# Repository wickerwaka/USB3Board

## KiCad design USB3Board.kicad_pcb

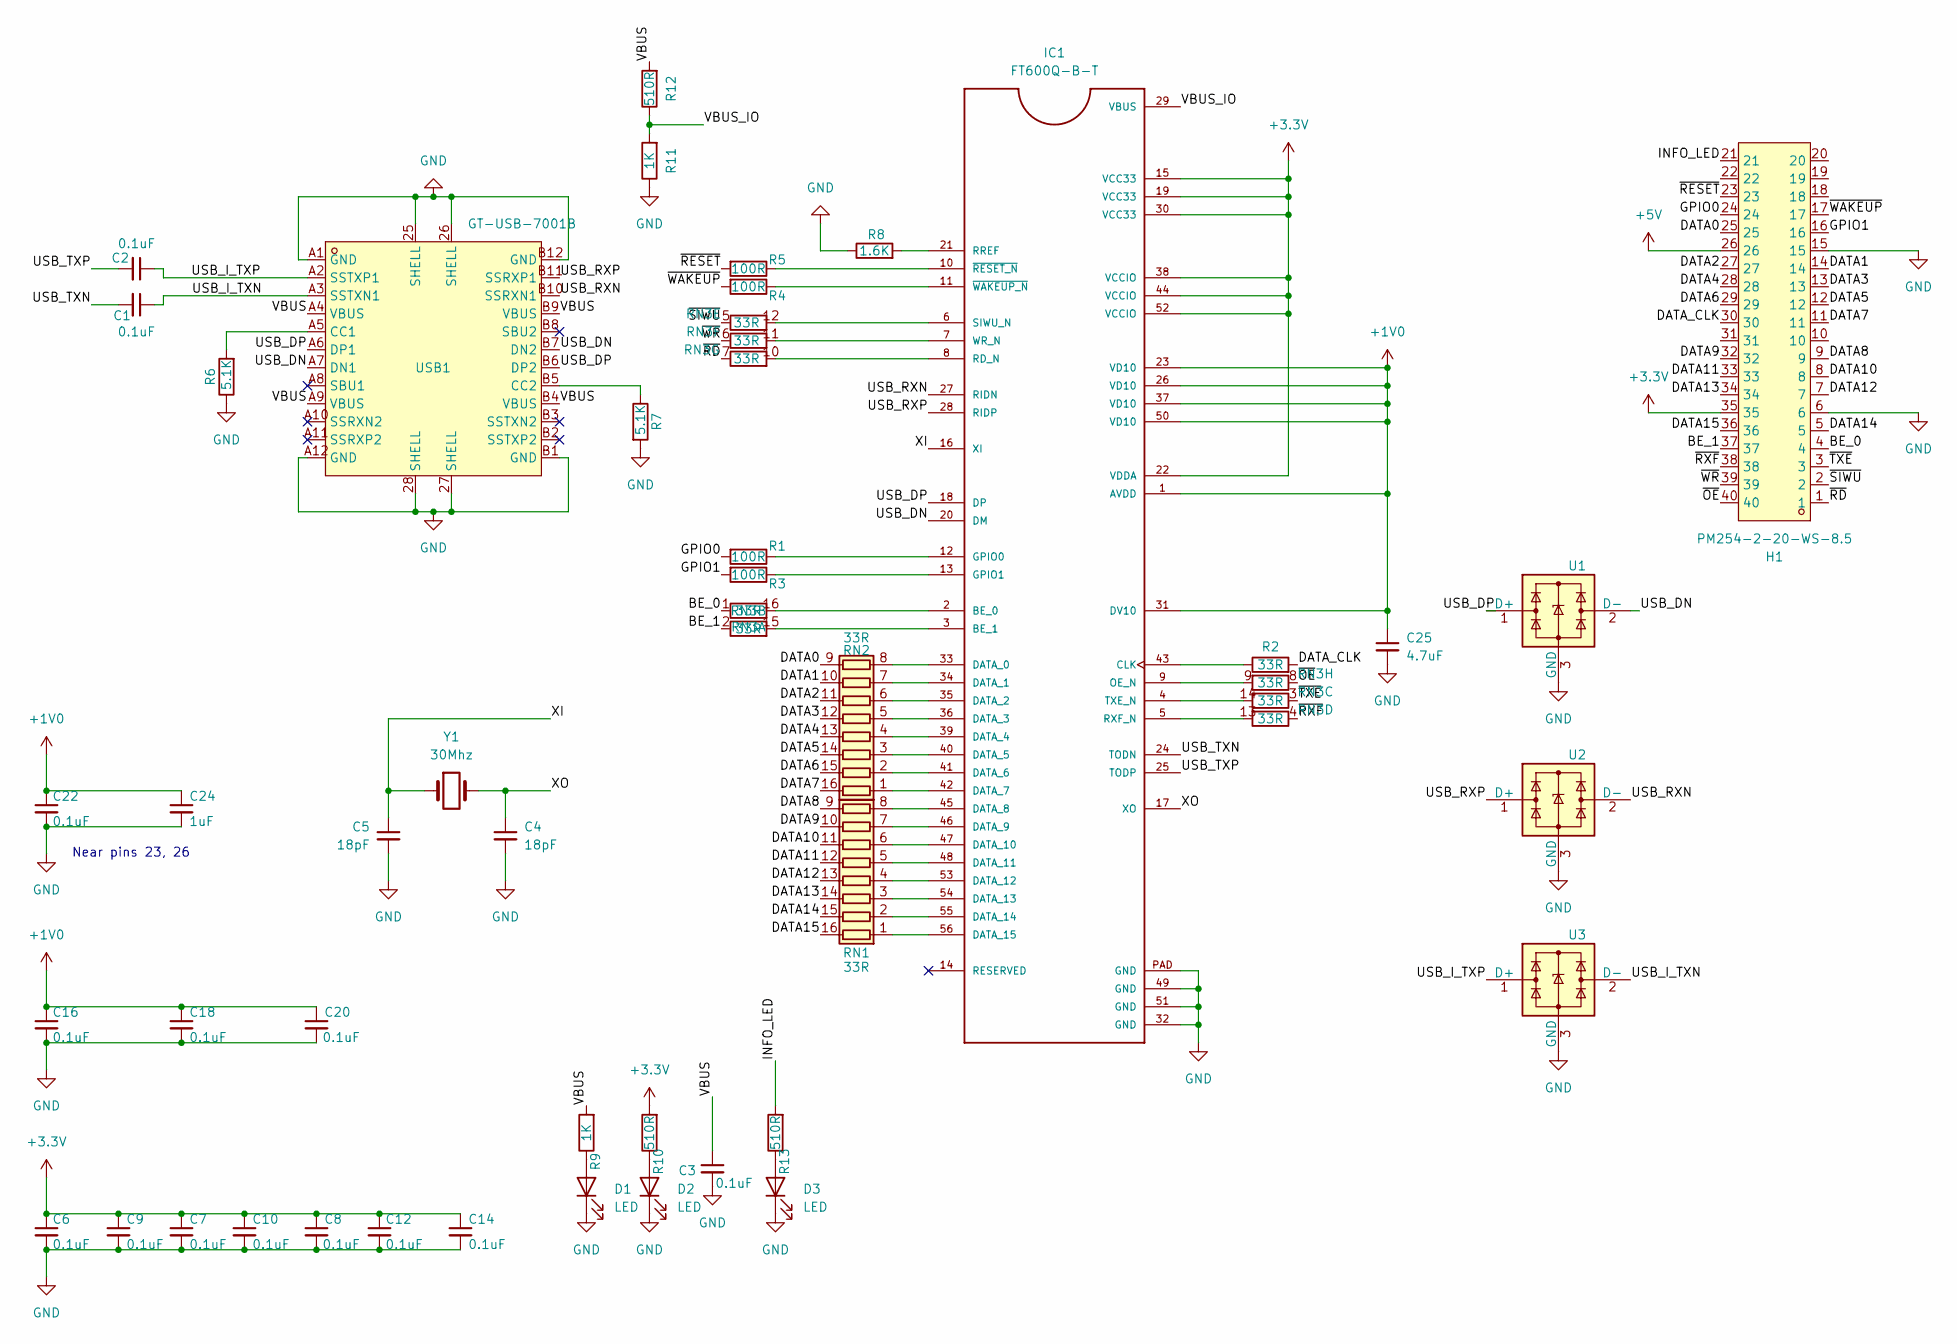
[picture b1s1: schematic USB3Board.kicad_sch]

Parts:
C1, C2, C3, C6, C7, C8, C9, C10, C12, C14, C16, C18, C20, C22: 0.1uF; C_0402_1005Metric; LCSC Part C1525
C4, C5: 18pF; C_0402_1005Metric; LCSC Part C1549
C24: 1uF; C_0402_1005Metric; LCSC Part C52923
C25: 4.7uF; C_0402_1005Metric; LCSC Part C23733
D1, D2: LED; LED_0603_1608Metric; LCSC Part C2984264
D3: LED; LED_0603_1608Metric; LCSC Part C2917175
H1: PM254-2-20-WS-8.5; HDR-SMD_40P-P2.54_PM254-2-20-WS-8.5; LCSC Part C5345531
IC1: FT600Q-B-T; QFN40P700X700X85-57N; LCSC Part C3227923
R1, R3, R4, R5: 100R; R_0402_1005Metric; LCSC Part C25076
R2: 33R; R_0402_1005Metric; LCSC Part C25105
R6, R7: 5.1K; R_0402_1005Metric; LCSC Part C105872
R8: 1.6K; R_0402_1005Metric; LCSC Part C4908
R9, R11: 1K; R_0402_1005Metric; LCSC Part C11702
R10, R12, R13: 510R; R_0402_1005Metric; LCSC Part C25123
RN1, RN2, RN3: 33R; RES-ARRAY-SMD_0402-16P-L4.0-W1.6-BL; LCSC Part C422182
U1, U2, U3: TPD2EUSB30; Texas_DRT-3; LCSC Part C97502
USB1: GT-USB-7001B; USB-C-SMD_GT-USB-7001B; LCSC Part C2843971
Y1: 30Mhz; Crystal_SMD_TXC_AX_8045-2Pin_8.0x4.5mm; LCSC Part C313042

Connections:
+1V0: C16.1, C18.1, C20.1, C22.1, C24.1, C25.1, IC1.1 (AVDD), IC1.23 (VD10), IC1.26 (VD10), IC1.31 (DV10), IC1.37 (VD10), IC1.50 (VD10)
+3.3V: C6.1, C7.1, C8.1, C9.1, C10.1, C12.1, C14.1, H1.35, IC1.15 (VCC33), IC1.19 (VCC33), IC1.22 (VDDA), IC1.30 (VCC33), IC1.38 (VCCIO), IC1.44 (VCCIO), IC1.52 (VCCIO), R10.2
+5V: H1.26
/BE_0: H1.4, RN3.1 (R1.1)
/BE_1: H1.37, RN3.2 (R2.1)
/DATA0: H1.25, RN2.9 (R8.2)
/DATA1: H1.14, RN2.10 (R7.2)
/DATA2: H1.27, RN2.11 (R6.2)
/DATA3: H1.13, RN2.12 (R5.2)
/DATA4: H1.28, RN2.13 (R4.2)
/DATA5: H1.12, RN2.14 (R3.2)
/DATA6: H1.29, RN2.15 (R2.2)
/DATA7: H1.11, RN2.16 (R1.2)
/DATA8: H1.9, RN1.9 (R8.2)
/DATA9: H1.32, RN1.10 (R7.2)
/DATA10: H1.8, RN1.11 (R6.2)
/DATA11: H1.33, RN1.12 (R5.2)
/DATA12: H1.7, RN1.13 (R4.2)
/DATA13: H1.34, RN1.14 (R3.2)
/DATA14: H1.5, RN1.15 (R2.2)
/DATA15: H1.36, RN1.16 (R1.2)
/DATA_CLK: H1.30, R2.2
/GPIO0: H1.24, R1.2
/GPIO1: H1.16, R3.2
/INFO_LED: H1.21, R13.2
/USB_DN: IC1.20 (DM), U1.2 (D-), USB1.A7 (DN1), USB1.B7 (DN2)
/USB_DP: IC1.18 (DP), U1.1 (D+), USB1.A6 (DP1), USB1.B6 (DP2)
/USB_I_TXN: C1.1, U3.2 (D-), USB1.A3 (SSTXN1)
/USB_I_TXP: C2.1, U3.1 (D+), USB1.A2 (SSTXP1)
/USB_RXN: IC1.27 (RIDN), U2.2 (D-), USB1.B10 (SSRXN1)
/USB_RXP: IC1.28 (RIDP), U2.1 (D+), USB1.B11 (SSRXP1)
/USB_TXN: C1.2, IC1.24 (TODN)
/USB_TXP: C2.2, IC1.25 (TODP)
/VBUS: C3.1, R9.2, R12.2, USB1.A4 (VBUS), USB1.A9 (VBUS), USB1.B4 (VBUS), USB1.B9 (VBUS)
/VBUS_IO: IC1.29 (VBUS), R11.2, R12.1
/XI: C5.1, IC1.16 (XI), Y1.1
/XO: C4.1, IC1.17 (XO), Y1.2
/~OE: H1.40, RN3.8 (R8.1)
/~RD: H1.1, RN3.7 (R7.1)
/~RESET: H1.23, R5.2
/~RXF: H1.38, RN3.4 (R4.1)
/~SIWU: H1.2, RN3.5 (R5.1)
/~TXE: H1.3, RN3.3 (R3.1)
/~WAKEUP: H1.17, R4.2
/~WR: H1.39, RN3.6 (R6.1)
GND: C3.2, C4.2, C5.2, C6.2, C7.2, C8.2, C9.2, C10.2, C12.2, C14.2, C16.2, C18.2, C20.2, C22.2, C24.2, C25.2, D1.1 (K), D2.1 (K), D3.1 (K), H1.6, H1.15, IC1.32 (GND), IC1.49 (GND), IC1.51 (GND), IC1.PAD (GND), R6.1, R7.2, R8.1, R11.1, U1.3 (GND), U2.3 (GND), U3.3 (GND), USB1.25 (SHELL), USB1.26 (SHELL), USB1.27 (SHELL), USB1.28 (SHELL), USB1.A1 (GND), USB1.A12 (GND), USB1.B1 (GND), USB1.B12 (GND)
unnamed: D1.2 (A), R9.1
unnamed: D2.2 (A), R10.1
unnamed: D3.2 (A), R13.1
unnamed: IC1.2 (BE_0), RN3.16 (R1.2)
unnamed: IC1.3 (BE_1), RN3.15 (R2.2)
unnamed: IC1.43 (CLK), R2.1
unnamed: IC1.33 (DATA_0), RN2.8 (R8.1)
unnamed: IC1.34 (DATA_1), RN2.7 (R7.1)
unnamed: IC1.35 (DATA_2), RN2.6 (R6.1)
unnamed: IC1.36 (DATA_3), RN2.5 (R5.1)
unnamed: IC1.39 (DATA_4), RN2.4 (R4.1)
unnamed: IC1.40 (DATA_5), RN2.3 (R3.1)
unnamed: IC1.41 (DATA_6), RN2.2 (R2.1)
unnamed: IC1.42 (DATA_7), RN2.1 (R1.1)
unnamed: IC1.45 (DATA_8), RN1.8 (R8.1)
unnamed: IC1.46 (DATA_9), RN1.7 (R7.1)
unnamed: IC1.47 (DATA_10), RN1.6 (R6.1)
unnamed: IC1.48 (DATA_11), RN1.5 (R5.1)
unnamed: IC1.53 (DATA_12), RN1.4 (R4.1)
unnamed: IC1.54 (DATA_13), RN1.3 (R3.1)
unnamed: IC1.55 (DATA_14), RN1.2 (R2.1)
unnamed: IC1.56 (DATA_15), RN1.1 (R1.1)
unnamed: IC1.12 (GPIO0), R1.1
unnamed: IC1.13 (GPIO1), R3.1
unnamed: IC1.9 (OE_N), RN3.9 (R8.2)
unnamed: IC1.8 (RD_N), RN3.10 (R7.2)
unnamed: IC1.21 (RREF), R8.2
unnamed: IC1.5 (RXF_N), RN3.13 (R4.2)
unnamed: IC1.6 (SIWU_N), RN3.12 (R5.2)
unnamed: IC1.4 (TXE_N), RN3.14 (R3.2)
unnamed: IC1.7 (WR_N), RN3.11 (R6.2)
unnamed: IC1.10 (~RESET_N), R5.1
unnamed: IC1.11 (~WAKEUP_N), R4.1
unnamed: R6.2, USB1.A5 (CC1)
unnamed: R7.1, USB1.B5 (CC2)

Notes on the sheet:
Near pins 23, 26

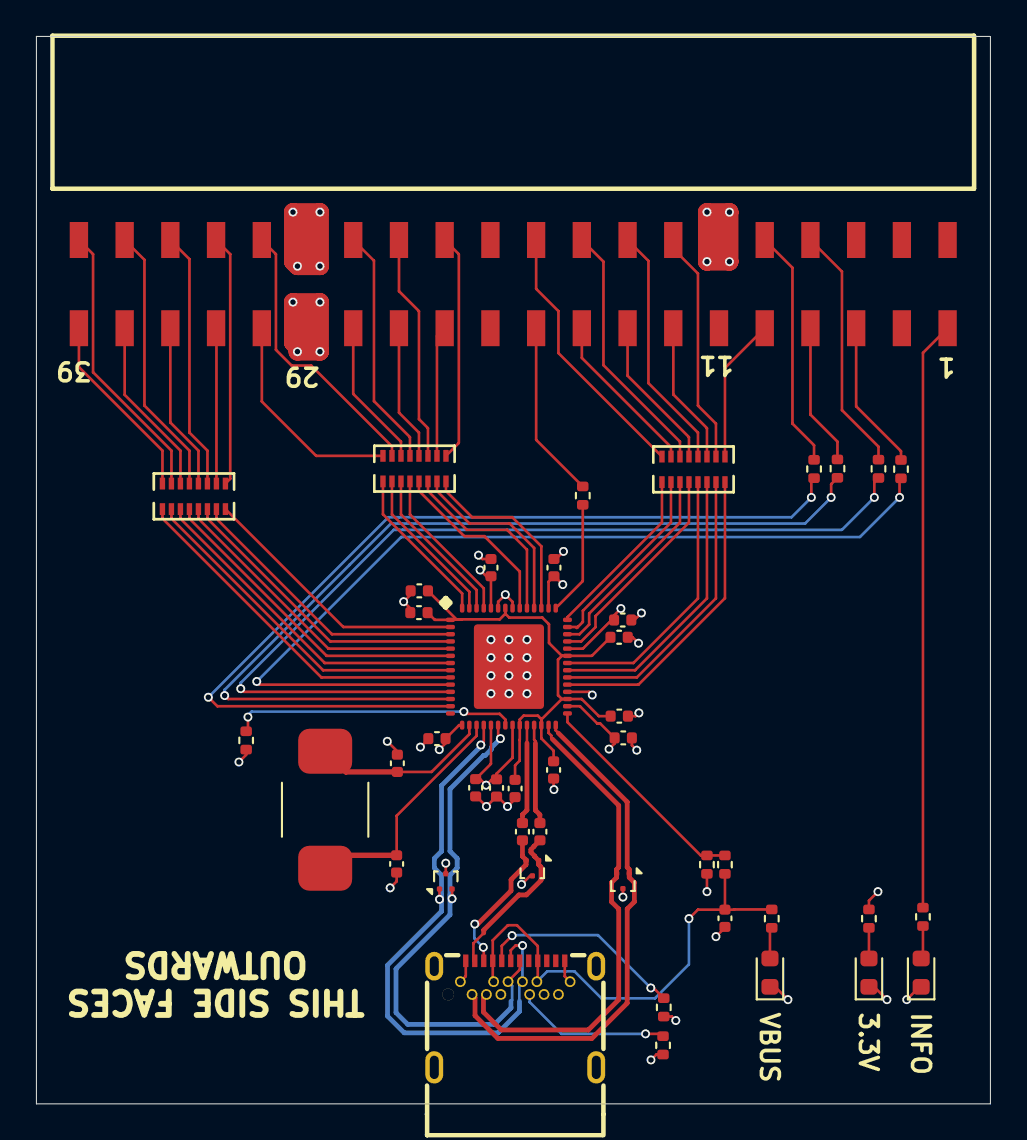
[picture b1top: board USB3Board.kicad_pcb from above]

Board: 4 copper layers, 53.0 x 59.3 mm, 44 parts (0 on the bottom side), 80 nets.

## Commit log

2024-06-08 1st pass
2024-06-08 Make via sizes consistent and large enough to not require special assembly Add some silkscreen to help orientation.
